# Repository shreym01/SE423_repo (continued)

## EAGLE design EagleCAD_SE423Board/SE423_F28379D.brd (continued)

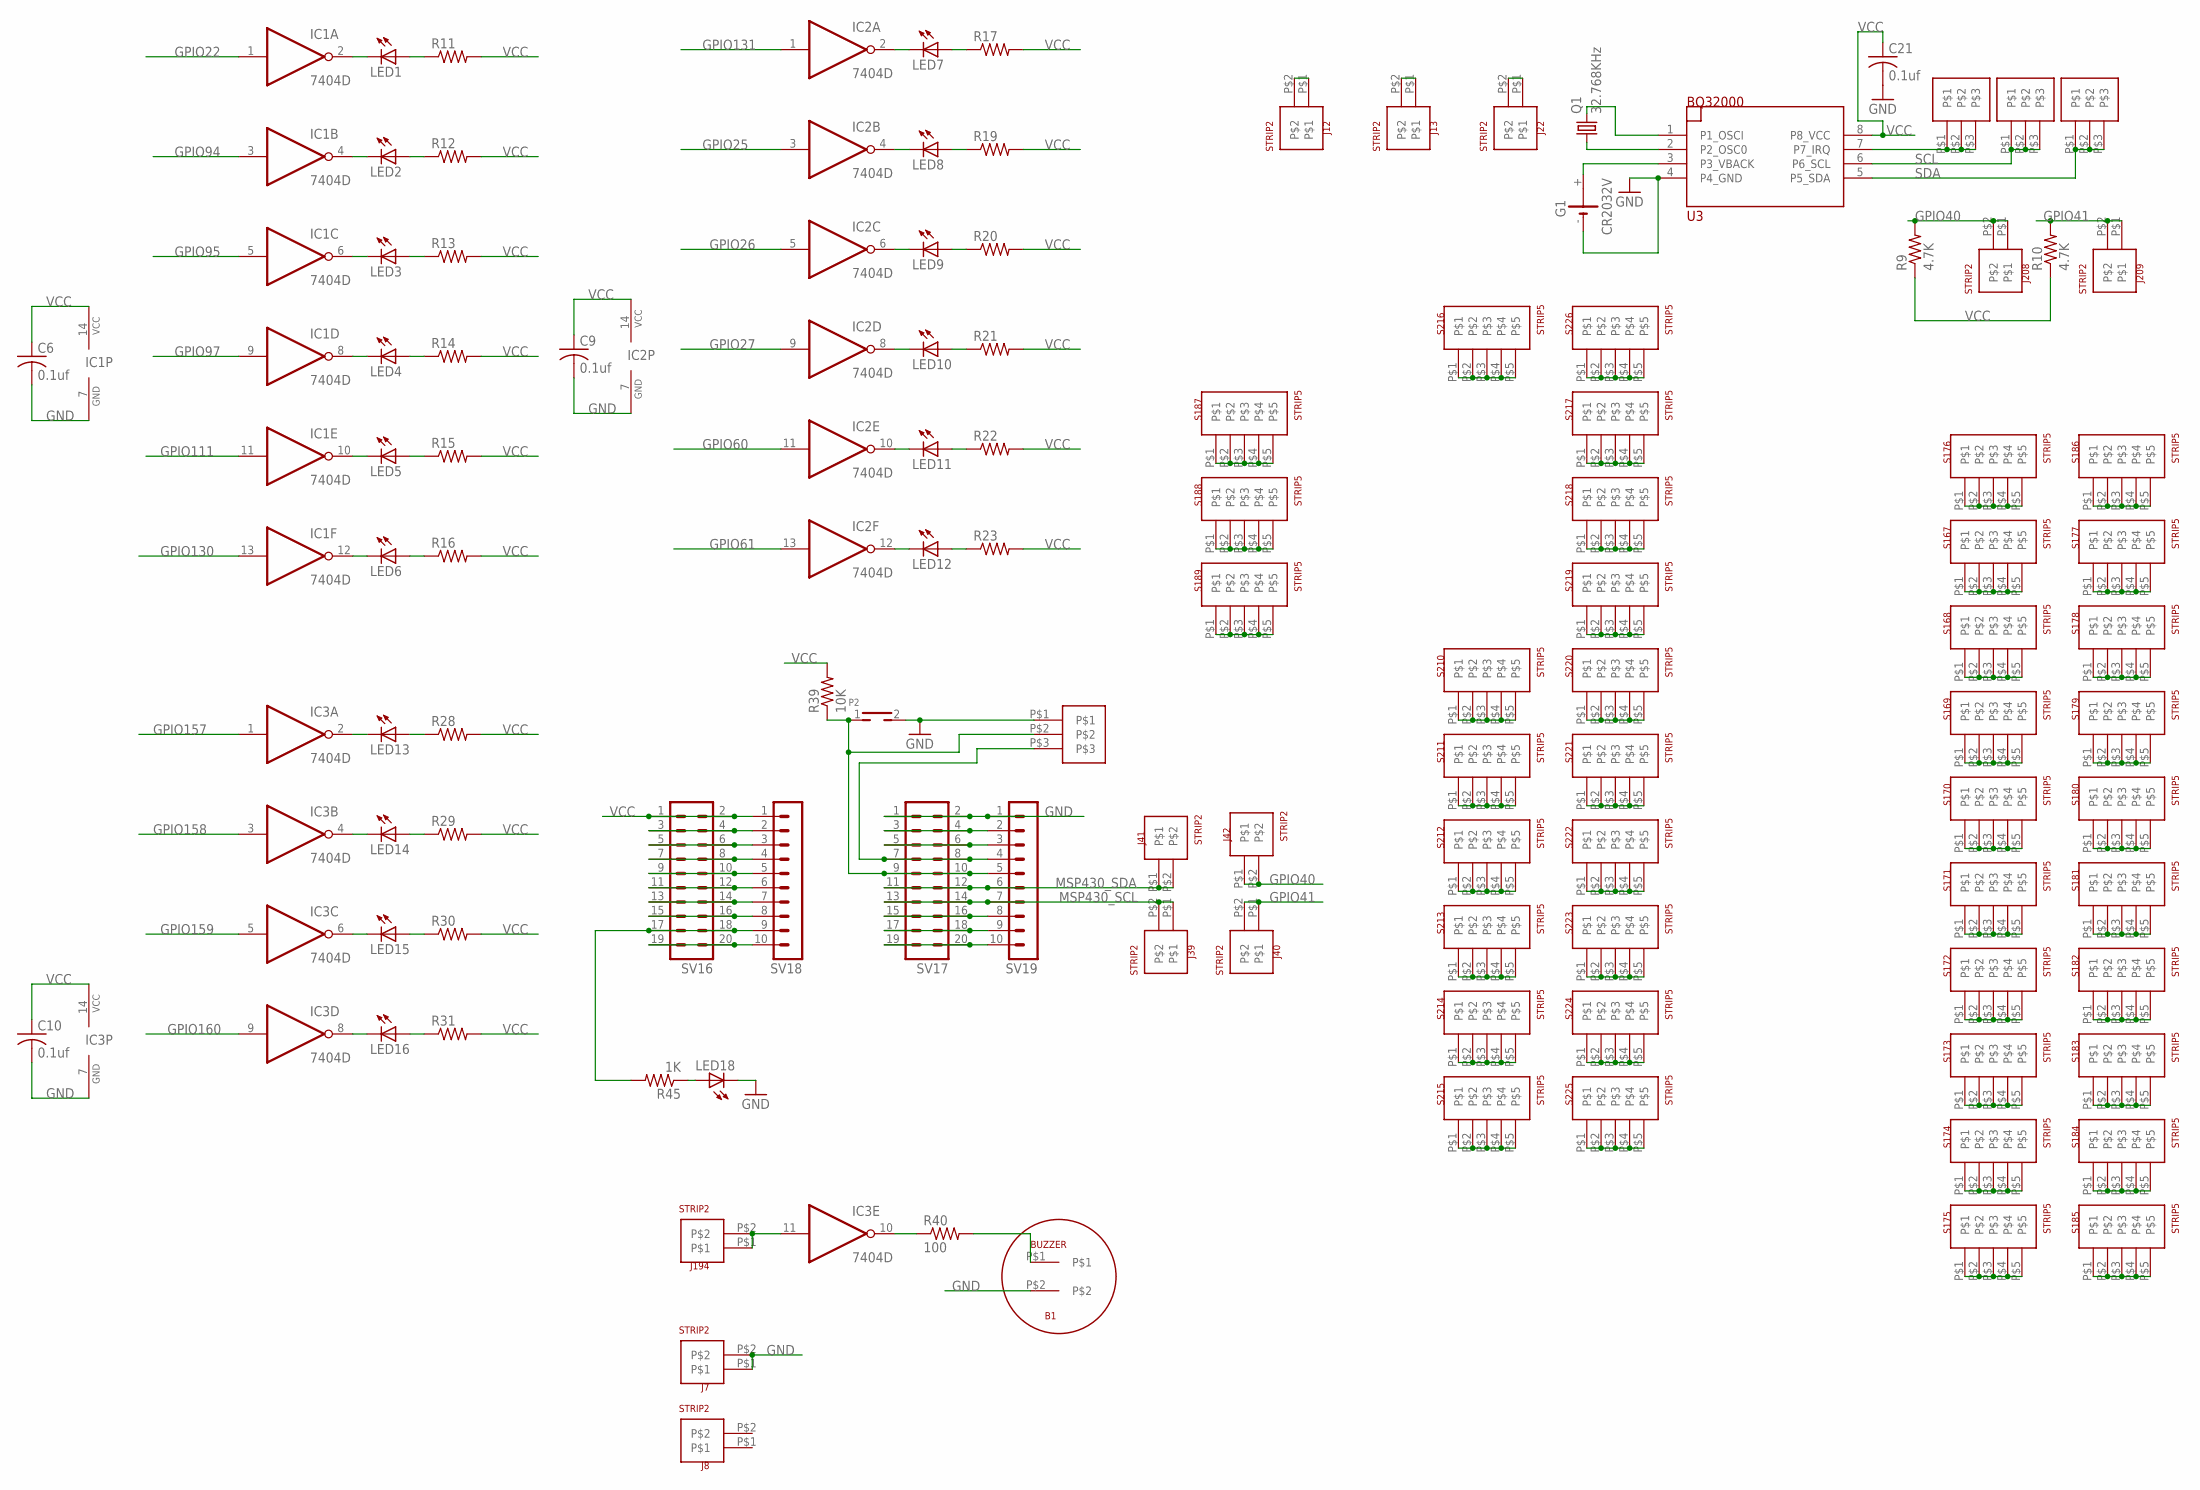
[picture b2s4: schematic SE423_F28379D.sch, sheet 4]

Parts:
B1: BUZZER
C6, C9, C10, C21: 0.1uf; C1206
G1: CR2032V
IC1, IC2, IC3: 7404D; SO14
J1, J2, J3, J43: STRIP3
J7, J8, J12, J13, J22, J39, J40, J41, J42, J194, J208, J209: STRIP2
LED1, LED2, LED3, LED4, LED5, LED6, LED7, LED8, LED9, LED10, LED11, LED12, LED13, LED14, LED15, LED16, LED18: LEDCHIPLED_1206; CHIPLED_1206
P2: TH_PUSHBOTTON; TH_PUSHBUTTON
Q1: 32.768KHz; TC26H
R9, R10: 4.7K; R1206
R11, R12, R13, R14, R15, R16, R17, R19, R20, R21, R22, R23, R28, R29, R30, R31: R-US_R1206; R1206
R39: 10K; R1206
R40: 100; R1206
R45: 1K; R1206
S167, S168, S169, S170, S171, S172, S173, S174, S175, S176, S177, S178, S179, S180, S181, S182, S183, S184, S185, S186, S187, S188, S189, S210, S211, S212, S213, S214, S215, S216, S217, S218, S219, S220, S221, S222, S223, S224, S225, S226: STRIP5
SV16, SV17: MA10-2
SV18, SV19: MA10-1
U3: BQ32000; SO08

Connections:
GND: B1.P$2, C6.2, C9.2, C10.2, C21.2, G1.-, IC1.7 (GND), IC2.7 (GND), IC3.7 (GND), J7.P$1, J7.P$2, J43.P$1, LED18.C, P2.2, SV17.1, SV17.2, SV19.1, U3.4 (P4_GND); also elsewhere on the board
GPIO22: IC1.1 (I); also elsewhere on the board
GPIO25: IC2.3 (I); also elsewhere on the board
GPIO26: IC2.5 (I); also elsewhere on the board
GPIO27: IC2.9 (I); also elsewhere on the board
GPIO40: J42.P$1, J42.P$2, J208.P$1, J208.P$2, R9.2; also elsewhere on the board
GPIO41: J40.P$1, J40.P$2, J209.P$1, J209.P$2, R10.2; also elsewhere on the board
GPIO60: IC2.11 (I); also elsewhere on the board
GPIO61: IC2.13 (I); also elsewhere on the board
GPIO94: IC1.3 (I); also elsewhere on the board
GPIO95: IC1.5 (I); also elsewhere on the board
GPIO97: IC1.9 (I); also elsewhere on the board
GPIO111: IC1.11 (I); also elsewhere on the board
GPIO130: IC1.13 (I); also elsewhere on the board
GPIO131: IC2.1 (I); also elsewhere on the board
GPIO157: IC3.1 (I); also elsewhere on the board
GPIO158: IC3.3 (I); also elsewhere on the board
GPIO159: IC3.5 (I); also elsewhere on the board
GPIO160: IC3.9 (I); also elsewhere on the board
MSP430_SCL: J39.P$1, J39.P$2, SV17.13, SV17.14, SV19.7
MSP430_SDA: J41.P$1, J41.P$2, SV17.11, SV17.12, SV19.6
unnamed: J12.P$1, J12.P$2
unnamed: J13.P$1, J13.P$2
unnamed: J22.P$1, J22.P$2
unnamed: R45.2, SV16.17, SV16.18, SV18.9
unnamed: SV16.3, SV16.4, SV18.2
unnamed: SV16.5, SV16.6, SV18.3
unnamed: SV16.7, SV16.8, SV18.4
unnamed: SV16.9, SV16.10, SV18.5
unnamed: SV16.11, SV16.12, SV18.6
unnamed: SV16.13, SV16.14, SV18.7
unnamed: SV16.15, SV16.16, SV18.8
unnamed: LED18.A, R45.1
unnamed: SV16.19, SV16.20, SV18.10
unnamed: SV17.3, SV17.4, SV19.2
unnamed: SV17.5, SV17.6, SV19.3
unnamed: J43.P$3, SV17.7, SV17.8, SV19.4
unnamed: SV17.15, SV17.16, SV19.8
unnamed: SV17.17, SV17.18, SV19.9
unnamed: SV17.19, SV17.20, SV19.10
unnamed: J43.P$2, P2.1, R39.1, SV17.9, SV17.10, SV19.5
unnamed: IC3.10 (O), R40.1
unnamed: B1.P$1, R40.2
unnamed: Q1.1, U3.2 (P2_OSC0)
unnamed: Q1.2, U3.1 (P1_OSCI)
unnamed: J1.P$1, J1.P$2, J1.P$3, U3.7 (P7_IRQ)
unnamed: G1.+, U3.3 (P3_VBACK)
unnamed: IC2.2 (O), LED7.C
unnamed: LED7.A, R17.1
unnamed: IC2.4 (O), LED8.C
unnamed: LED8.A, R19.1
unnamed: IC2.6 (O), LED9.C
unnamed: S167.P$1, S167.P$2, S167.P$3, S167.P$4, S167.P$5
unnamed: S168.P$1, S168.P$2, S168.P$3, S168.P$4, S168.P$5
unnamed: S169.P$1, S169.P$2, S169.P$3, S169.P$4, S169.P$5
unnamed: S170.P$1, S170.P$2, S170.P$3, S170.P$4, S170.P$5
unnamed: S171.P$1, S171.P$2, S171.P$3, S171.P$4, S171.P$5
unnamed: S172.P$1, S172.P$2, S172.P$3, S172.P$4, S172.P$5
unnamed: S173.P$1, S173.P$2, S173.P$3, S173.P$4, S173.P$5
unnamed: S174.P$1, S174.P$2, S174.P$3, S174.P$4, S174.P$5
unnamed: S175.P$1, S175.P$2, S175.P$3, S175.P$4, S175.P$5
unnamed: S176.P$1, S176.P$2, S176.P$3, S176.P$4, S176.P$5
unnamed: S177.P$1, S177.P$2, S177.P$3, S177.P$4, S177.P$5
unnamed: S178.P$1, S178.P$2, S178.P$3, S178.P$4, S178.P$5
unnamed: S179.P$1, S179.P$2, S179.P$3, S179.P$4, S179.P$5
unnamed: S180.P$1, S180.P$2, S180.P$3, S180.P$4, S180.P$5
unnamed: S181.P$1, S181.P$2, S181.P$3, S181.P$4, S181.P$5
unnamed: S182.P$1, S182.P$2, S182.P$3, S182.P$4, S182.P$5
unnamed: S183.P$1, S183.P$2, S183.P$3, S183.P$4, S183.P$5
unnamed: S184.P$1, S184.P$2, S184.P$3, S184.P$4, S184.P$5
unnamed: S185.P$1, S185.P$2, S185.P$3, S185.P$4, S185.P$5
unnamed: S186.P$1, S186.P$2, S186.P$3, S186.P$4, S186.P$5
unnamed: S187.P$1, S187.P$2, S187.P$3, S187.P$4, S187.P$5
unnamed: S188.P$1, S188.P$2, S188.P$3, S188.P$4, S188.P$5
unnamed: S189.P$1, S189.P$2, S189.P$3, S189.P$4, S189.P$5
unnamed: S210.P$1, S210.P$2, S210.P$3, S210.P$4, S210.P$5
unnamed: S211.P$1, S211.P$2, S211.P$3, S211.P$4, S211.P$5
unnamed: S212.P$1, S212.P$2, S212.P$3, S212.P$4, S212.P$5
unnamed: S213.P$1, S213.P$2, S213.P$3, S213.P$4, S213.P$5
unnamed: S214.P$1, S214.P$2, S214.P$3, S214.P$4, S214.P$5
unnamed: S215.P$1, S215.P$2, S215.P$3, S215.P$4, S215.P$5
unnamed: S216.P$1, S216.P$2, S216.P$3, S216.P$4, S216.P$5
unnamed: S217.P$1, S217.P$2, S217.P$3, S217.P$4, S217.P$5
unnamed: S218.P$1, S218.P$2, S218.P$3, S218.P$4, S218.P$5
unnamed: S219.P$1, S219.P$2, S219.P$3, S219.P$4, S219.P$5
unnamed: S220.P$1, S220.P$2, S220.P$3, S220.P$4, S220.P$5
unnamed: S221.P$1, S221.P$2, S221.P$3, S221.P$4, S221.P$5
unnamed: S222.P$1, S222.P$2, S222.P$3, S222.P$4, S222.P$5
unnamed: S223.P$1, S223.P$2, S223.P$3, S223.P$4, S223.P$5
unnamed: S224.P$1, S224.P$2, S224.P$3, S224.P$4, S224.P$5
unnamed: S225.P$1, S225.P$2, S225.P$3, S225.P$4, S225.P$5
unnamed: S226.P$1, S226.P$2, S226.P$3, S226.P$4, S226.P$5
unnamed: IC1.2 (O), LED1.C
unnamed: LED1.A, R11.1
unnamed: IC1.4 (O), LED2.C
unnamed: LED2.A, R12.1
unnamed: IC1.6 (O), LED3.C
unnamed: LED3.A, R13.1
unnamed: IC1.8 (O), LED4.C
unnamed: LED4.A, R14.1
unnamed: IC1.10 (O), LED5.C
unnamed: LED5.A, R15.1
unnamed: IC1.12 (O), LED6.C
unnamed: LED6.A, R16.1
unnamed: LED9.A, R20.1
unnamed: IC2.8 (O), LED10.C
unnamed: LED10.A, R21.1
unnamed: IC2.10 (O), LED11.C
unnamed: LED11.A, R22.1
unnamed: IC2.12 (O), LED12.C
unnamed: LED12.A, R23.1
unnamed: IC3.2 (O), LED13.C
unnamed: LED13.A, R28.1
unnamed: IC3.4 (O), LED14.C
unnamed: LED14.A, R29.1
unnamed: IC3.6 (O), LED15.C
unnamed: LED15.A, R30.1
unnamed: IC3.8 (O), LED16.C
unnamed: LED16.A, R31.1
unnamed: IC3.11 (I), J194.P$1, J194.P$2
SCL: J2.P$1, J2.P$2, J2.P$3, U3.6 (P6_SCL)
SDA: J3.P$1, J3.P$2, J3.P$3, U3.5 (P5_SDA)
VCC: C6.1, C9.1, C10.1, C21.1, IC1.14 (VCC), IC2.14 (VCC), IC3.14 (VCC), R9.1, R10.1, R11.2, R12.2, R13.2, R14.2, R15.2, R16.2, R17.2, R19.2, R20.2, R21.2, R22.2, R23.2, R28.2, R29.2, R30.2, R31.2, R39.2, SV16.1, SV16.2, SV18.1, U3.8 (P8_VCC); also elsewhere on the board

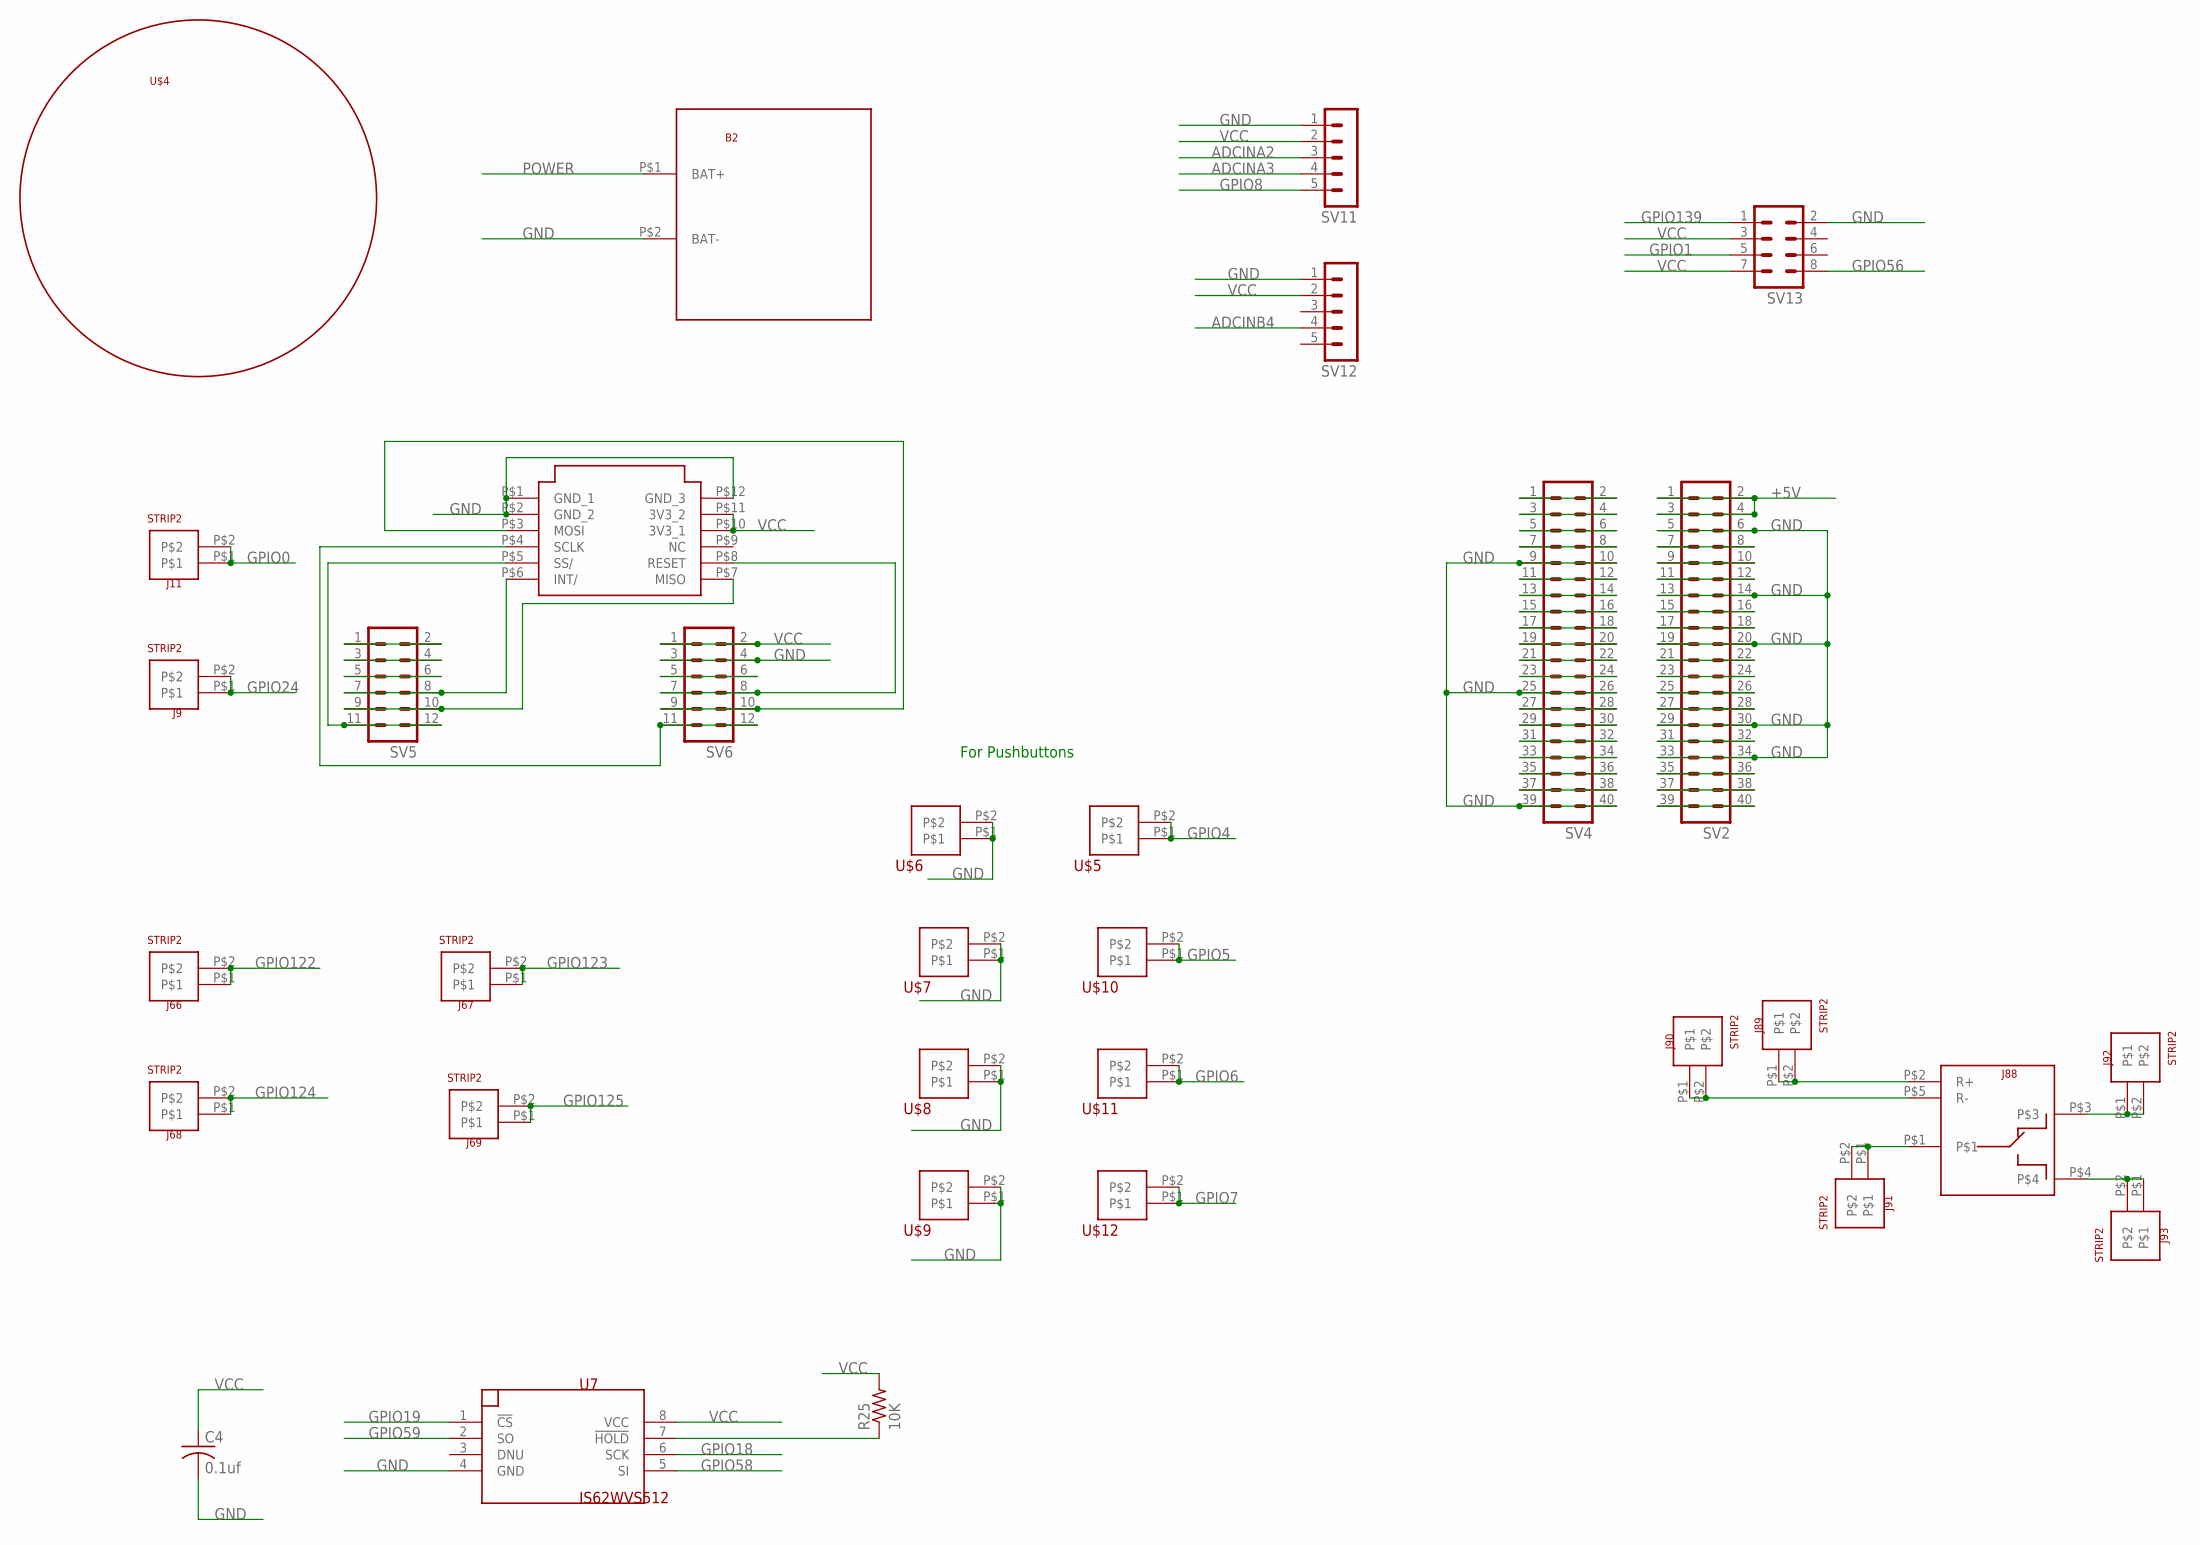
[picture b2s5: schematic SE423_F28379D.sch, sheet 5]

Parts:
B2: BATTERY_4AA_HOLDER
C4: 0.1uf; C1206
ETH1: USR_ES1_W5500
J9, J11, J66, J67, J68, J69, J89, J90, J91, J92, J93: STRIP2
J88: RELAY_JQC-3F_5V
R25: 10K; M1206
SV2, SV4: MA20-2
SV5, SV6: MA06-2
SV11, SV12: MA05-1
SV13: MA04-2
U7: IS62WVS512; SO08
U$4: CASTERWHEEL
U$5, U$6, U$7, U$8, U$9, U$10, U$11, U$12: 2PIN50MIL

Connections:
+5V: SV2.1, SV2.2, SV2.3, SV2.4; also elsewhere on the board
ADCINA2: SV11.3; also elsewhere on the board
ADCINA3: SV11.4; also elsewhere on the board
ADCINB4: SV12.4; also elsewhere on the board
GND: B2.P$2 (BAT-), C4.2, ETH1.P$1 (GND_1), ETH1.P$2 (GND_2), ETH1.P$12 (GND_3), SV2.5, SV2.6, SV2.13, SV2.14, SV2.19, SV2.20, SV2.29, SV2.30, SV2.33, SV2.34, SV4.9, SV4.10, SV4.25, SV4.26, SV4.39, SV4.40, SV6.3, SV6.4, SV11.1, SV12.1, SV13.2, U7.4 (GND), U$6.P$1, U$6.P$2, U$7.P$1, U$7.P$2, U$8.P$1, U$8.P$2, U$9.P$1, U$9.P$2; also elsewhere on the board
GPIO0: J11.P$1, J11.P$2; also elsewhere on the board
GPIO1: SV13.5; also elsewhere on the board
GPIO4: U$5.P$1, U$5.P$2; also elsewhere on the board
GPIO5: U$10.P$1, U$10.P$2; also elsewhere on the board
GPIO6: U$11.P$1, U$11.P$2; also elsewhere on the board
GPIO7: U$12.P$1, U$12.P$2; also elsewhere on the board
GPIO8: SV11.5; also elsewhere on the board
GPIO18: U7.6 (SCK); also elsewhere on the board
GPIO19: U7.1 (!CS); also elsewhere on the board
GPIO24: J9.P$1, J9.P$2; also elsewhere on the board
GPIO56: SV13.8; also elsewhere on the board
GPIO58: U7.5 (SI); also elsewhere on the board
GPIO59: U7.2 (SO); also elsewhere on the board
GPIO122: J66.P$1, J66.P$2; also elsewhere on the board
GPIO123: J67.P$1, J67.P$2; also elsewhere on the board
GPIO124: J68.P$1, J68.P$2; also elsewhere on the board
GPIO125: J69.P$1, J69.P$2; also elsewhere on the board
GPIO139: SV13.1; also elsewhere on the board
unnamed: R25.1, U7.7 (!HOLD)
unnamed: SV4.1, SV4.2
unnamed: SV5.1, SV5.2
unnamed: SV5.3, SV5.4
unnamed: SV5.5, SV5.6
unnamed: SV4.3, SV4.4
unnamed: SV4.5, SV4.6
unnamed: SV4.7, SV4.8
unnamed: ETH1.P$6 (INT/), SV5.7, SV5.8
unnamed: SV4.11, SV4.12
unnamed: SV4.13, SV4.14
unnamed: SV4.15, SV4.16
unnamed: SV4.17, SV4.18
unnamed: SV4.19, SV4.20
unnamed: SV4.21, SV4.22
unnamed: SV4.23, SV4.24
unnamed: ETH1.P$7 (MISO), SV5.9, SV5.10
unnamed: SV4.27, SV4.28
unnamed: SV4.29, SV4.30
unnamed: SV4.31, SV4.32
unnamed: SV4.33, SV4.34
unnamed: SV4.35, SV4.36
unnamed: SV4.37, SV4.38
unnamed: ETH1.P$5 (SS/), SV5.11, SV5.12
unnamed: SV2.39, SV2.40
unnamed: SV2.37, SV2.38
unnamed: SV2.35, SV2.36
unnamed: SV2.31, SV2.32
unnamed: SV2.27, SV2.28
unnamed: SV2.25, SV2.26
unnamed: SV2.23, SV2.24
unnamed: SV2.21, SV2.22
unnamed: SV6.5, SV6.6
unnamed: SV2.17, SV2.18
unnamed: SV2.15, SV2.16
unnamed: ETH1.P$8 (RESET), SV6.7, SV6.8
unnamed: SV2.11, SV2.12
unnamed: SV2.9, SV2.10
unnamed: SV2.7, SV2.8
unnamed: ETH1.P$3 (MOSI), SV6.9, SV6.10
unnamed: ETH1.P$4 (SCLK), SV6.11, SV6.12
unnamed: J88.P$2 (R+), J89.P$1, J89.P$2
unnamed: J88.P$5 (R-), J90.P$1, J90.P$2
unnamed: J88.P$1, J91.P$1, J91.P$2
unnamed: J88.P$3, J92.P$1, J92.P$2
unnamed: J88.P$4, J93.P$1, J93.P$2
POWER: B2.P$1 (BAT+); also elsewhere on the board
VCC: C4.1, ETH1.P$10 (3V3_1), ETH1.P$11 (3V3_2), R25.2, SV6.1, SV6.2, SV11.2, SV12.2, SV13.3, SV13.7, U7.8 (VCC); also elsewhere on the board

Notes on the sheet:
For Pushbuttons

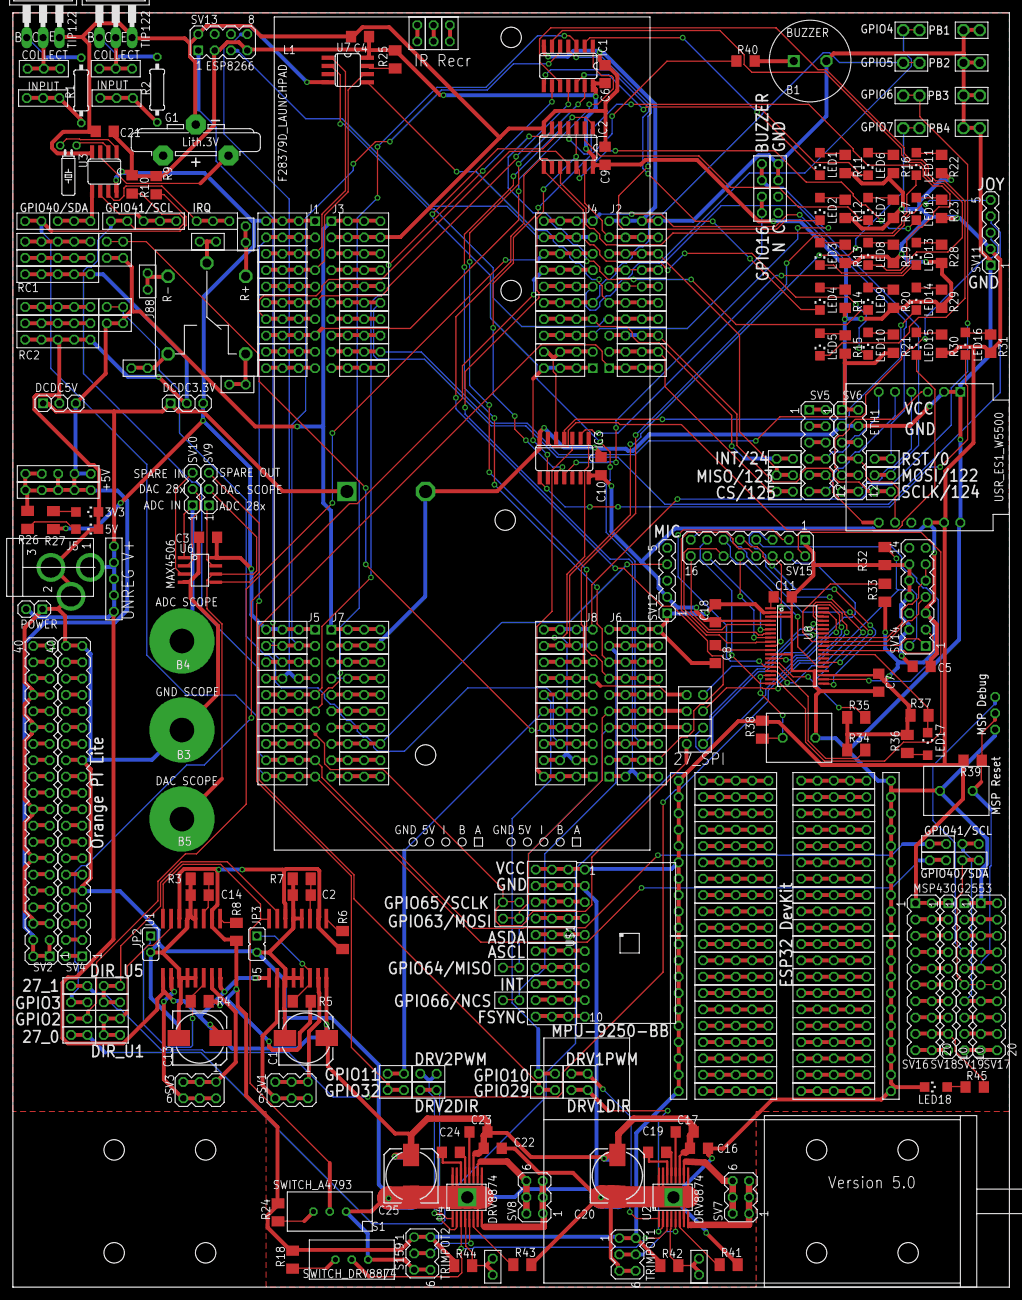
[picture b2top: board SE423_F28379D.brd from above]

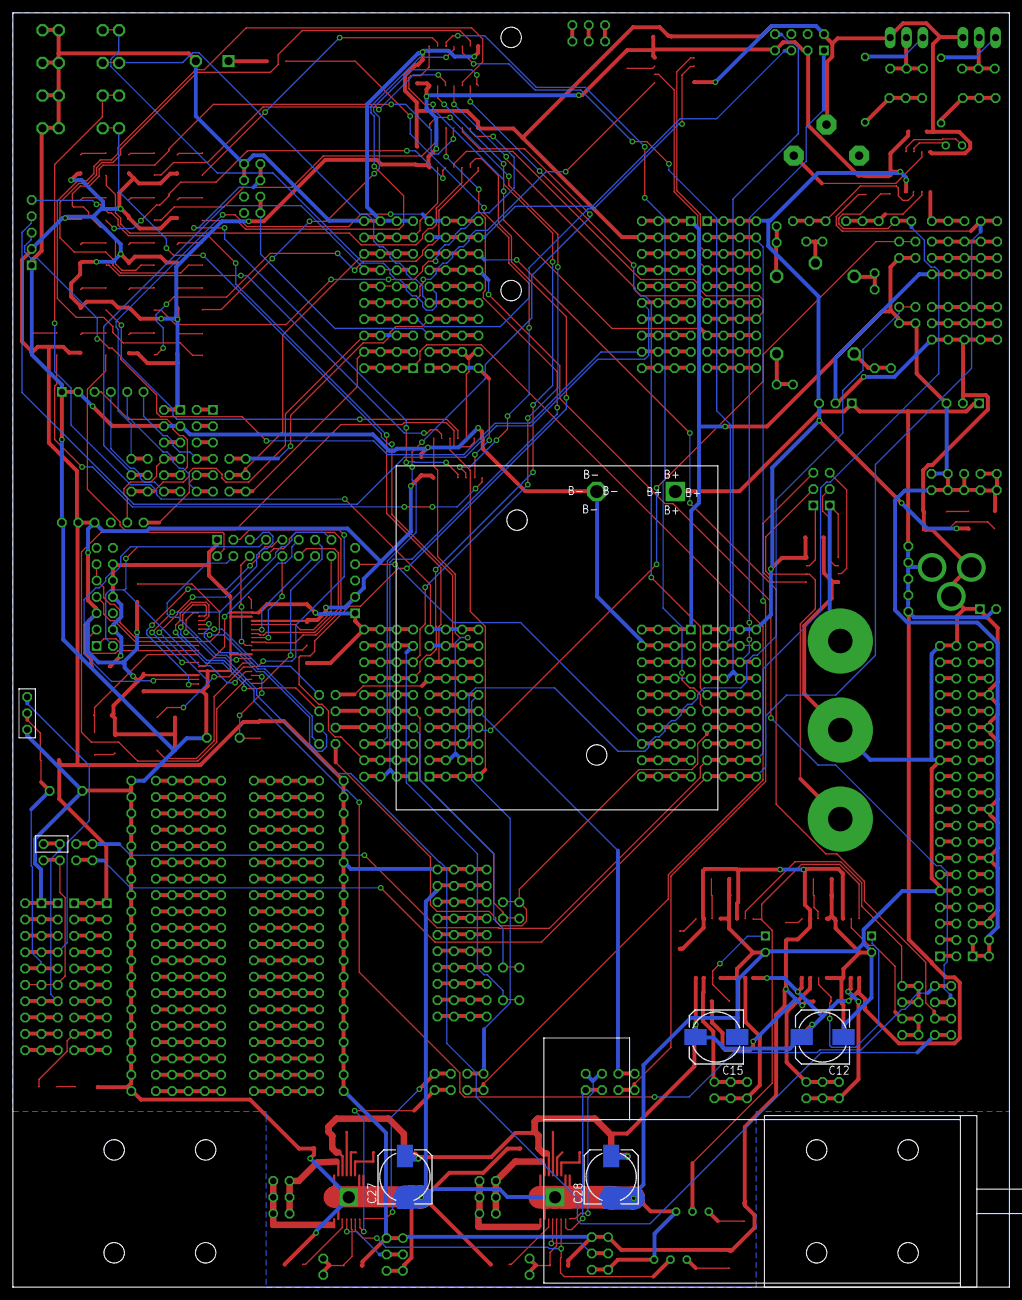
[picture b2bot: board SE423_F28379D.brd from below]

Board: 2 copper layers, 154.9 x 198.1 mm, 363 parts (8 on the bottom side), 318 nets.

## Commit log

2025-01-11 Added note about F28027code
2025-01-30 finish lab 1
2025-02-06 finish lab 2
2025-02-13 Finish comments lab 2
2025-02-13 updawg
2025-02-20 lab 3 done
2025-02-27 lab 3
2025-03-06 Root beer
2025-03-13 lab 5
2025-03-27 lab6 p1
2025-03-31 added make shm to serial_COMandOpti Makefile
2025-04-03 hate
2025-04-07 AprilTag Starter
2025-04-10 update files
2025-04-10 update v2
2025-04-10 lab 6
2025-04-12 Changed ManualBlob_STARTER a few things
2025-04-12 Changed so April tag viewing can be shut off
2025-04-16 Added some comments about rio in OpenMV code
2025-04-17 ooga booga
2025-04-22 Fixed some small issues with AstarStarters
2025-04-24 added AstarProjectwithCANAprilStarter
2025-04-24 Lab 7
2025-04-29 Cleaned up OpenMV folder a bit
2025-05-01 color
2025-05-01 renamed stuff
2025-05-01 labview picture mapping
2025-05-08 ball color servo stuff:)
2025-05-08 april tag pathing,started
2025-05-09 left wall following start
2025-05-09 finished left wall following
2025-05-11 broke :(
2025-05-13 code
2025-05-13 sdasdada
2025-05-13 Update FinalProjectwithCANAprilStarter_main_vvmz.c
    FIX COMMENTS
2025-05-13 Update FinalProjectwithCANAprilStarter_main.c
    FIX NAME FR
